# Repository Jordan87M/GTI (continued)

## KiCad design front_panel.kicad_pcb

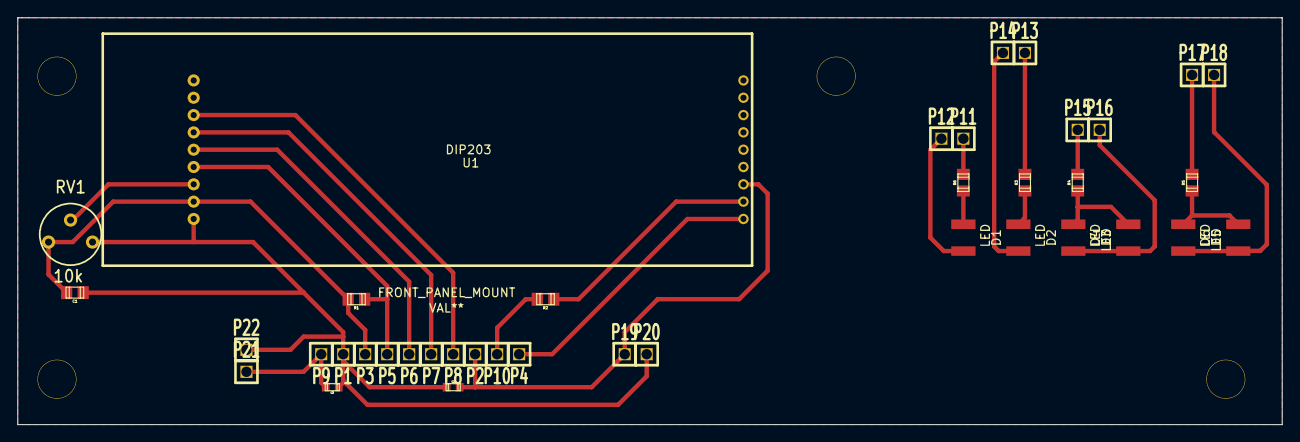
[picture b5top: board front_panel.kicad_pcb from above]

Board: 2 copper layers, 146.1 x 47.0 mm, 40 parts (0 on the bottom side), 24 nets.

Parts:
C1: .47u; c_0805
C2, C3: 100n; c_0603
D1, D2, D3, D4, D5, D6: LED; 1209
FRONT_PANEL_MOUNT: VAL**; FRONT_PANEL_MOUNT
P1: GNDA; MOLEX-1
P2: RESETn; MOLEX-1
P3: 3V_IN; MOLEX-1
P4: PWM; MOLEX-1
P5: SPI1_CS2; MOLEX-1
P6: SPI1_MOSI; MOLEX-1
P7: SPI1_SCK; MOLEX-1
P8: SPI1_MISO; MOLEX-1
P9: PROGRAM_INT; MOLEX-1
P10: 5V_FRONT; MOLEX-1
P11: DC_LINK+; MOLEX-1
P12: DC_LINK-; MOLEX-1
P13: DC_RAIL+; MOLEX-1
P14: DC_RAIL-; MOLEX-1
P15: AC_OUT_A; MOLEX-1
P16: AC_OUT_B; MOLEX-1
P17: GRID_REF_A; MOLEX-1
P18: GRID_REF_B; MOLEX-1
P19: RESET_SWITCH; MOLEX-1
P20: RESET_SWITCH_GND; MOLEX-1
P21: PROGRAM_SWITCH; MOLEX-1
P22: PROGRAM_SWITCH_GND; MOLEX-1
R1: 10k; c_0805
R2: 18; c_0805
R3, R4, R5, R6: 2.2k; c_0805
RV1: 10k; RV2
U1: DIP203

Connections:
GNDA: C1.2, C2.2, C3.2, P1.1, P20.1, P22.1, RV1.3, U1.1
unnamed: R2.2, U1.17
unnamed: P10.1, R2.1
unnamed: P4.1, U1.18
unnamed: RV1.2, U1.3
unnamed: P7.1, U1.6
unnamed: P6.1, U1.5
unnamed: C2.1, P2.1, P19.1, U1.16
unnamed: D1.1, R6.2
unnamed: D2.1, R3.2
unnamed: P11.1, R6.1
unnamed: P13.1, R3.1
unnamed: P15.1, R4.1
unnamed: D3.1, D4.2, R4.2
unnamed: D1.2, P12.1
unnamed: D2.2, P14.1
unnamed: D3.2, D4.1, P16.1
unnamed: P8.1, U1.7
unnamed: P5.1, R1.2, U1.4
unnamed: D5.1, D6.2, R5.2
unnamed: P17.1, R5.1
unnamed: D5.2, D6.1, P18.1
unnamed: C3.1, P9.1, P21.1
VCC: C1.1, P3.1, R1.1, RV1.1, U1.2

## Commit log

2016-02-24 first tracked version. includes interrupt logic, temperature sensor, and FET heat sink pour.
2016-03-19 updating converter daughterboard for compatibility with DAC trimming for use with DCMG
2016-03-20 added protection circuitry to converter daughterboard. should be ready for fabrication
2016-03-20 added silkscreen labels
2016-03-25 updated converter board and created fab files
2016-04-13 revised converter daughterboard to adjust setpoint signal to account for current dropped across low side sense resistor
